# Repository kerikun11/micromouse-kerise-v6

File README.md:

# MicroMouse KERISE v6

けりの第6作目マイクロマウス

## 回路設計

- KiCad

## 機体設計

- Fusion 360

## ソフトウェア開発

- PlatformIO Espressif32 ESP-IDF

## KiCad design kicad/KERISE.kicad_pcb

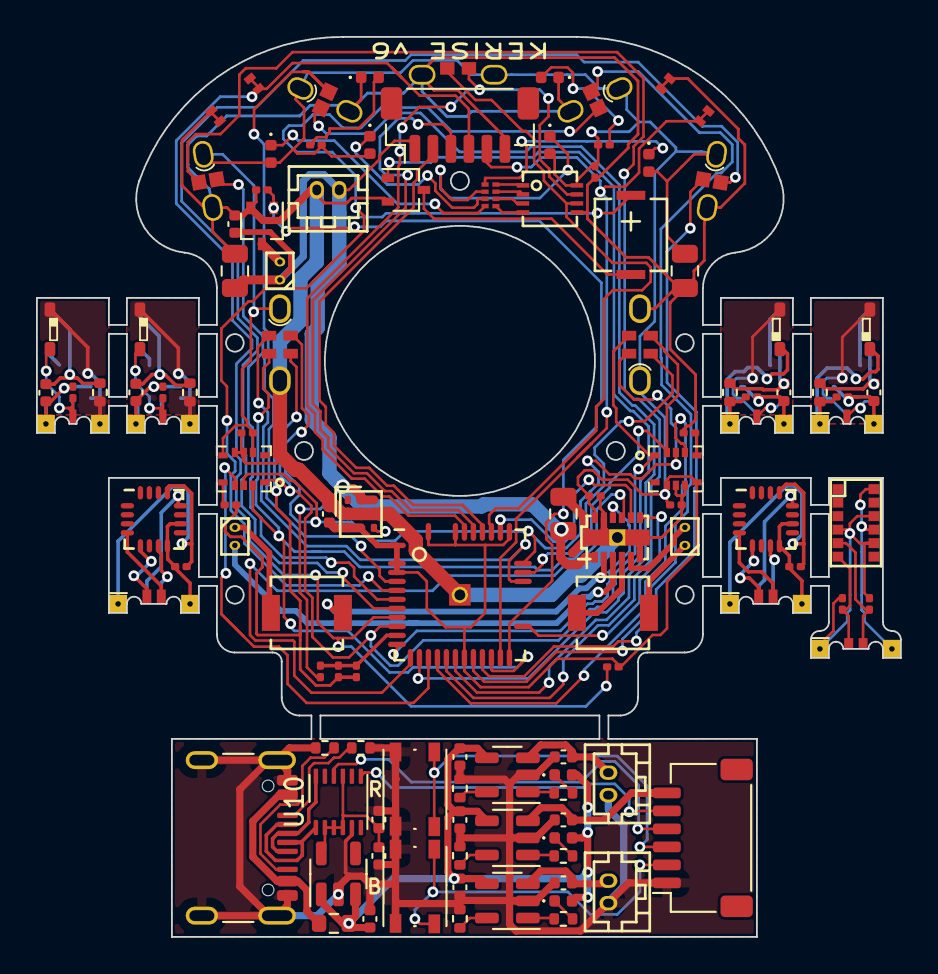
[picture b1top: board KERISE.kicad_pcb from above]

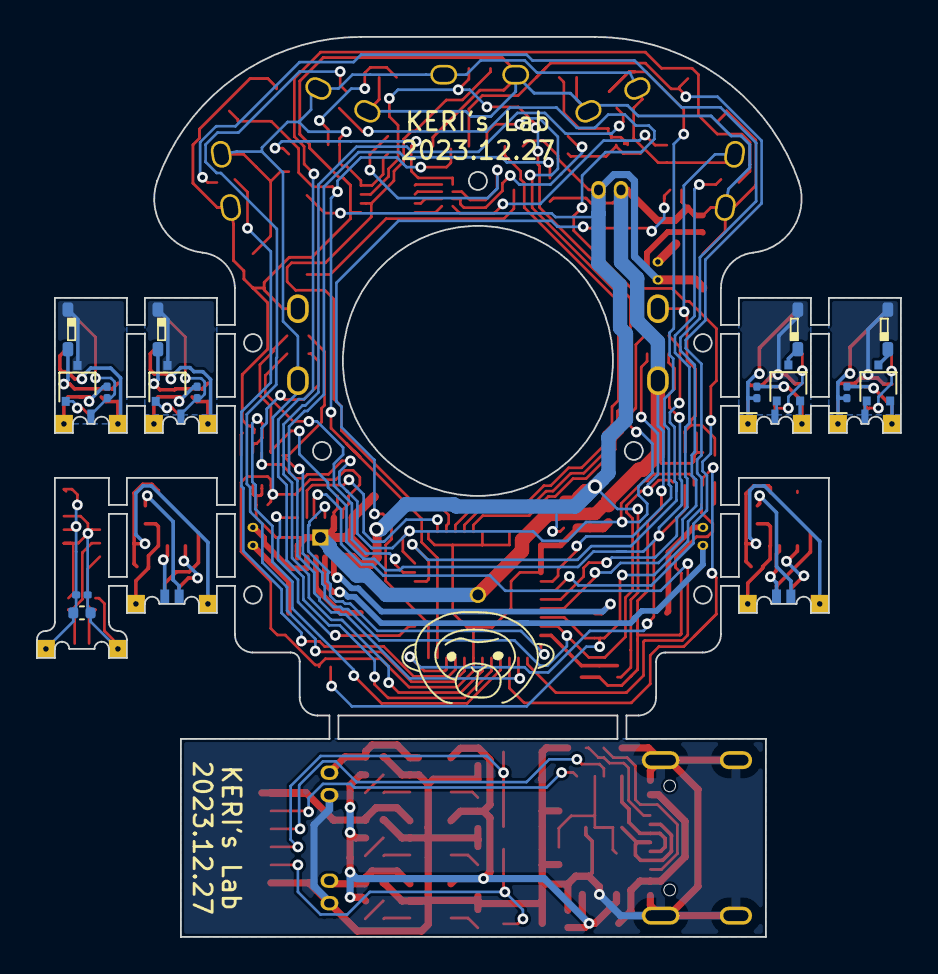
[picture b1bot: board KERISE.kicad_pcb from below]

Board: 2 copper layers, 48.0 x 50.0 mm, 127 parts (16 on the bottom side), 115 nets.

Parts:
BT1: Battery; Hirose_DF13-02P-1.25DSA_02x1.25mm_Straight
C1, C4: 10u; C_0402_1005Metric
C2, C3, C5, C6, C7, C8, C10, C12, C14, C16, C18, C19, C20, C24, C25: 0.1u; C_0201_0603Metric
C9, C11, C13, C15: 1u; C_0402_1005Metric
C17, C21, C22: 47u; C_0805_2012Metric
C23, C29, C30, C31, C32, C33, C34: 4.7u; C_0402_1005Metric
C26, C27: 0.1u; C_0402_1005Metric
C28: 0.47u; C_0402_1005Metric
D1, D2, D3, D4: APDA3020F3C-P22; APDA3020
D5, D6: Power; LED_0402_1005Metric
D7, D8, D9, D10, D11, D12, D13: LED; LED_0402_1005Metric
F1: MF-FSMF035X-2; R_0603_1608Metric
J1: COM; JST_SH_BM06B-SRSS-TB_1x06-1MP_P1.00mm_Vertical
J2, J4: ENC_Host; STAND_HOST_06
J3, J5: ENC_Slave; STAND_SLAVE_06
J6: Fan; SMD_conn_2
J7, J9, J11, J13: Ref_Host; IR_HOST_V_04
J8, J10, J12, J14: Ref_Slave; IR_SLAVE_V_04
J15: Motor_L; SMD_conn_2
J16: Motor_R; SMD_conn_2
J17: COM; JST_SH_SM06B-SRSS-TB_1x06-1MP_P1.00mm_Horizontal
J18: 5077CR-16-SMC2-BK-TR; USB_C_Receptacle_GCT_USB4105-xx-A_16P_TopMnt_Horizontal
J19: Charge1; Hirose_DF13-02P-1.25DSA_02x1.25mm_Straight
J20: Charge2; Hirose_DF13-02P-1.25DSA_02x1.25mm_Straight
L1, L2: 47u; L_4018
LS1: SMT-0440-S-R
P1: ToF_Host; STAND_HOST_04
P2: ToF_Slave; STAND_SLAVE_04
Q1, Q2, Q4, Q6, Q8, Q10: DMN3065LW-7; SOT-323_SC-70
Q3, Q5, Q7, Q9: APDA3020P3C-P22; APDA3020
R1, R2, R4, R6, R8, R10, R11, R12: 10k; R_0201_0603Metric
R3, R5, R7, R9: 100; R_0402_1005Metric
R13, R14: 1k; R_0201_0603Metric
R15, R16: 4.7k; R_0201_0603Metric
R17, R18: 5.1k; R_0402_1005Metric
R19, R20, R21: 1k; R_0402_1005Metric
R22, R23, R24: 10k; R_0402_1005Metric
RN1: EXB-18V102JX; R_Array_Concave_4x0201
SW1: RESET; EVPBB
SW2: UPLOAD; EVPBB
SW3: RESET; SW_Push_1P1T_NO_Vertical_Wuerth_434133025816
SW4: BOOT; SW_Push_1P1T_NO_Vertical_Wuerth_434133025816
U1: ESP32-PICO-V3-02
U2, U3: MA730
U4, U5: ICM-20600
U6: DRV8835
U7: LXDC2URxx; LXDC2UR
U8: VL6180X
U9: PCA9632; DFN-8-1EP_3x3mm_Pitch0.5mm
U10: FT234XD; DFN-12-1EP_3x3mm_P0.5mm_EP1.6x2.5mm
U11: NJM2863F33; TSOT-23-5
U12, U13, U14: MCP73831-2-OT; SOT-23-5

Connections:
+3.3V: C1.2, C5.1, C7.1, C19.1, C22.1, C25.1, D7.2 (A), D8.2 (A), D9.2 (A), D10.2 (A), J2.1, J4.1, J7.1, J9.1, J11.1, J13.1, P1.1, R1.2, R13.1, R14.1, U1.1 (VDDA), U1.3 (VDD3P3), U1.4 (VDD3P3), U1.19 (VDD3P3_RTC), U1.37 (VDD3P3_CPU), U1.43 (VDDA), U1.46 (VDDA), U4.5 (VDDIO), U4.8 (VDD), U5.5 (VDDIO), U5.8 (VDD), U6.12 (VCC), U7.3 (Vout), U7.4 (Vout), U9.8 (VDD)
+BATT: BT1.1 (+), C4.1, C17.1, C18.1, C21.1, J1.1, J6.1, LS1.1, R11.1, U6.1 (VM), U7.5 (EN), U7.7 (Vin), U7.8 (Vin)
/Encoder_L/s_CS: J3.2, U2.5 (~CS)
/Encoder_L/s_GND: C2.2, J3.6, U2.8 (GND), U2.10 (TEST)
/Encoder_L/s_MISO: J3.5, U2.7 (MISO)
/Encoder_L/s_MOSI: J3.4, U2.4 (MOSI)
/Encoder_L/s_SCLK: J3.3, U2.12 (SCLK)
/Encoder_L/s_VDD: C2.1, J3.1, U2.13 (VDD)
/Encoder_R/s_CS: J5.2, U3.5 (~CS)
/Encoder_R/s_GND: C3.2, J5.6, U3.8 (GND), U3.10 (TEST)
/Encoder_R/s_MISO: J5.5, U3.7 (MISO)
/Encoder_R/s_MOSI: J5.4, U3.4 (MOSI)
/Encoder_R/s_SCLK: J5.3, U3.12 (SCLK)
/Encoder_R/s_VDD: C3.1, J5.1, U3.13 (VDD)
/Fan/fan_to_fet: J6.2, Q1.3 (D)
/Flash/BAT: C34.1, J17.6, U14.3 (V_{BAT})
/Flash/BAT_CH1: C32.1, J19.1, U12.3 (V_{BAT})
/Flash/BAT_CH2: C33.1, J20.1, U13.3 (V_{BAT})
/Flash/ESP32_BT: J17.2, SW4.1
/Flash/ESP32_EN: J17.3, SW3.1
/Flash/ESP32_RX: J17.5, U10.7 (TXD)
/Flash/ESP32_TX: J17.4, U10.10 (RXD)
/Flash/GND: C26.1, C27.2, C28.2, C29.2, C30.2, C31.2, C32.2, C33.2, C34.2, J17.1, J18.A1 (GND), J18.A12 (GND), J18.B1 (GND), J18.B12 (GND), J18.S1 (SHIELD), J19.2, J20.2, R17.2, R18.2, R22.2, R23.2, R24.2, SW3.2, SW4.2, U10.5 (GND), U11.2 (GND), U12.2 (V_{SS}), U13.2 (V_{SS}), U14.2 (V_{SS})
/Flash/USB_D+: J18.A6 (D+), J18.B6 (D+), U10.12 (USBDP)
/Flash/USB_D-: J18.A7 (D-), J18.B7 (D-), U10.1 (USBDM)
/Flash/VBUS: C27.1, C29.1, C30.1, C31.1, D11.2 (A), D12.2 (A), D13.2 (A), F1.2, U11.1 (VIN), U11.3 (~SHDN), U12.4 (V_{DD}), U13.4 (V_{DD}), U14.4 (V_{DD})
/Flash/VBUS_FUSE: F1.1, J18.A4 (VBUS), J18.A9 (VBUS), J18.B4 (VBUS), J18.B9 (VBUS)
/Flash/VCC: C26.2, C28.1, U10.2 (RESET#), U10.3 (3V3OUT), U10.4 (VCC), U10.9 (VCCIO), U11.5 (VOUT)
/IR_RCV_FL/LED_to_C: C9.1, D1.2 (A), R3.2
/IR_RCV_FL/LED_to_FET: D1.1 (K), Q2.3 (D)
/IR_RCV_FL/s_3.3V: C10.1, J8.1, Q3.1 (C), R3.1
/IR_RCV_FL/s_GND: C9.2, C10.2, J8.4, Q2.2 (S), R4.2
/IR_RCV_FL/s_IR_LED: J8.2, Q2.1 (G)
/IR_RCV_FL/s_IR_RCV: J8.3, Q3.2 (E), R4.1
/IR_RCV_FR/LED_to_C: C11.1, D2.2 (A), R5.2
/IR_RCV_FR/LED_to_FET: D2.1 (K), Q4.3 (D)
/IR_RCV_FR/s_3.3V: C12.1, J10.1, Q5.1 (C), R5.1
/IR_RCV_FR/s_GND: C11.2, C12.2, J10.4, Q4.2 (S), R6.2
/IR_RCV_FR/s_IR_LED: J10.2, Q4.1 (G)
/IR_RCV_FR/s_IR_RCV: J10.3, Q5.2 (E), R6.1
/IR_RCV_SL/LED_to_C: C13.1, D3.2 (A), R7.2
/IR_RCV_SL/LED_to_FET: D3.1 (K), Q6.3 (D)
/IR_RCV_SL/s_3.3V: C14.1, J12.1, Q7.1 (C), R7.1
/IR_RCV_SL/s_GND: C13.2, C14.2, J12.4, Q6.2 (S), R8.2
/IR_RCV_SL/s_IR_LED: J12.2, Q6.1 (G)
/IR_RCV_SL/s_IR_RCV: J12.3, Q7.2 (E), R8.1
/IR_RCV_SR/LED_to_C: C15.1, D4.2 (A), R9.2
/IR_RCV_SR/LED_to_FET: D4.1 (K), Q8.3 (D)
/IR_RCV_SR/s_3.3V: C16.1, J14.1, Q9.1 (C), R9.1
/IR_RCV_SR/s_GND: C15.2, C16.2, J14.4, Q8.2 (S), R10.2
/IR_RCV_SR/s_IR_LED: J14.2, Q8.1 (G)
/IR_RCV_SR/s_IR_RCV: J14.3, Q9.2 (E), R10.1
/Motor/MT_OUT_L1: J15.1, L1.1
/Motor/MT_OUT_L2: J15.2, U6.3 (AOUT2)
/Motor/MT_OUT_L_L: L1.2, U6.2 (AOUT1)
/Motor/MT_OUT_L_R: L2.2, U6.4 (BOUT1)
/Motor/MT_OUT_R1: J16.1, L2.1
/Motor/MT_OUT_R2: J16.2, U6.5 (BOUT2)
/ToF/s_3.3V: C23.1, C24.1, P2.1, R15.1, R16.1, U8.4 (GPIO0/CE), U8.8 (AVDD_VCSEL), U8.10 (AVDD)
/ToF/s_GND: C23.2, C24.2, P2.4, U8.9 (AVSS_VCSEL), U8.12 (AVSS)
/ToF/s_SCL: P2.3, R16.2, U8.5 (SCL)
/ToF/s_SDA: P2.2, R15.2, U8.6 (SDA)
BAT-VOL: C20.1, R11.2, R12.1, U1.11 (GPI35/VDET_2/ADC1_CH7)
BUTTON: J1.5, SW2.1, U1.23 (*GPIO0/ADC2_CH1/TOUCH1/CLK_OUT1/EMAC_TX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)
ENABLE: J1.4, R1.1, SW1.1, U1.9 (CHIP_PU)
FAN: Q1.1 (G), R2.1, U1.24 (GPIO4/ADC2_CH0/TOUCH0/HSPIHD/HS2_DATA1/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)
GND: BT1.2 (-), C1.1, C4.2, C5.2, C6.2, C7.2, C8.2, C17.2, C18.2, C19.2, C20.2, C21.2, C22.2, C25.2, D5.1 (K), D6.1 (K), J1.6, J2.6, J4.6, J7.4, J9.4, J11.4, J13.4, P1.4, Q1.2 (S), Q10.2 (S), R2.2, R12.2, SW1.2, SW2.2, U1.49 (GND), U4.6 (GND), U4.7 (RESV), U5.6 (GND), U5.7 (RESV), U6.6 (GND), U6.11 (MODE), U6.13 (GNDP), U7.2 (GND), U7.6 (GND), U7.9 (GND), U9.5 (VSS)
I2C-SCL: P1.3, U1.39 (GPIO22/VSPIWP/U0RTS/EMAC_TXD1), U9.6 (SCL)
I2C-SDA: P1.2, U1.42 (GPIO21/VSPIHD/EMAC_TX_EN), U9.7 (SDA)
MT-IN-L1: U1.12 (GPIO32/32K_XP/ADC1_CH4/TOUCH9), U6.10 (AIN1)
MT-IN-L2: U1.13 (GPIO33/32K_XN/ADC1_CH5/TOUCH8), U6.9 (AIN2)
MT-IN-R1: U1.38 (GPIO19/VSPIQ/U0CTS/EMAC_TXD0), U6.8 (BIN1)
MT-IN-R2: U1.27 (GPIO20), U6.7 (BIN2)
unnamed: D5.2 (A), R13.2
unnamed: D6.2 (A), R14.2
unnamed: D7.1 (K), RN1.5 (R4.2)
unnamed: D8.1 (K), RN1.6 (R3.2)
unnamed: D9.1 (K), RN1.7 (R2.2)
unnamed: D10.1 (K), RN1.8 (R1.2)
unnamed: D11.1 (K), R19.1
unnamed: D12.1 (K), R20.1
unnamed: D13.1 (K), R21.1
unnamed: J18.A5 (CC1), R18.1
unnamed: J18.B5 (CC2), R17.1
unnamed: LS1.2, Q10.3 (D)
unnamed: RN1.1 (R1.1), U9.4 (LED3)
unnamed: RN1.2 (R2.1), U9.3 (LED2)
unnamed: RN1.3 (R3.1), U9.2 (LED1)
unnamed: RN1.4 (R4.1), U9.1 (LED0)
unnamed: C6.1, U4.11 (REGOUT)
unnamed: C8.1, U5.11 (REGOUT)
unnamed: R22.1, U12.5 (PROG)
unnamed: R19.2, U12.1 (STAT)
unnamed: R23.1, U13.5 (PROG)
unnamed: R20.2, U13.1 (STAT)
unnamed: R24.1, U14.5 (PROG)
unnamed: R21.2, U14.1 (STAT)
PR-LED-FL: J7.2, U1.17 (GPIO14/ADC2_CH6/TOUCH6/MTMS/HSPI_CLK/HS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)
PR-LED-FR: J9.2, U1.21 (*GPIO15/ADC2_CH3/TOUCH3/MTDO/HSPICS0/HS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)
PR-LED-SL: J11.2, U1.18 (*GPIO12/ADC2_CH5/TOUCH5/MTDI/HSPIQ/HS2_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)
PR-LED-SR: J13.2, U1.20 (GPIO13/ADC2_CH4/TOUCH4/MTCK/HSPID/HS2_D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)
PR-RCV-FL: J7.3, U1.7 (GPI38/SENSOR_CAPN/ADC1_CH2)
PR-RCV-FR: J9.3, U1.8 (GPI39/SENSOR_VN/ADC1_CH3)
PR-RCV-SL: J11.3, U1.5 (GPI36/SENSOR_VP/ADC1_CH0)
PR-RCV-SR: J13.3, U1.6 (GPI37/SENSOR_CAPP/ADC1_CH1)
SPEAKER: Q10.1 (G), U1.14 (GPIO25/DAC_1/ADC2_CH8)
SPI-CS-ENC-L: J2.2, U1.32 (GPIO7/SD_DATA0/SPIQ/HS1_DATA0/U2RTS)
SPI-CS-ENC-R: J4.2, U1.33 (GPIO8/SD_DATA1/SPID/HS1_DATA1/U2CTS)
SPI-CS-IMU-L: U1.15 (GPIO26/DAC_2/ADC2_CH9), U4.12 (~CS)
SPI-CS-IMU-R: U1.16 (GPIO27/ADC2_CH7/TOUCH7), U5.12 (~CS)
SPI-MISO: J2.5, J4.5, U1.10 (GPI34/VDET_1/ADC1_CH6), U4.1 (SA0/SDO), U5.1 (SA0/SDO)
SPI-MOSI: J2.4, J4.4, U1.22 (*GPIO2/ADC2_CH2/TOUCH2/HSPIWP/HS2_DATA0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), U4.14 (SDA/SDI), U5.14 (SDA/SDI)
SPI-SCLK: J2.3, J4.3, U1.34 (*GPIO5/VSPICS0/HS1_DATA6/EMAC_RX_CLK), U4.13 (SCL/SCLK), U5.13 (SCL/SCLK)
UART-RX: J1.2, U1.40 (GPIO3/U0RXD/CLK_OUT2)
UART-TX: J1.3, U1.41 (GPIO1/U0TXD/CLK_OUT3/EMAC_RXD2)

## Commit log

2023-12-30 initial commit (empty)
2023-12-30 設計中のファイルを追加
2023-12-30 自動配線完了
2023-12-30 とりあえず配線完了
2023-12-30 Elecrowの指摘を修正
2023-12-30 1回目の基板修正
2023-12-30 READMEを追加
